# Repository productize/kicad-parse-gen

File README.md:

# kicad-parse-gen
rust kicad file code

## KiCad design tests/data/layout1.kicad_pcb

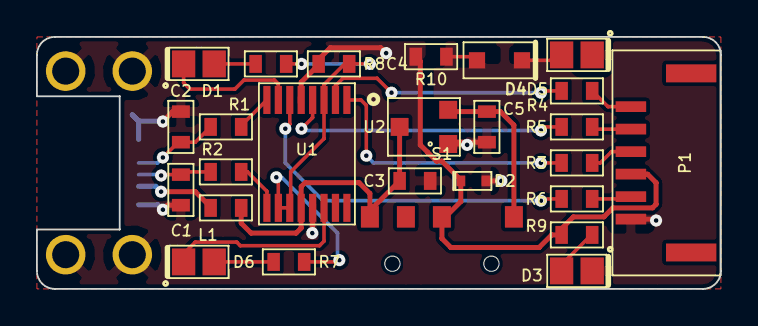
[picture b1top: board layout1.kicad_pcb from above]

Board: 2 copper layers, 38.0 x 14.0 mm, 27 parts (1 on the bottom side), 25 nets.

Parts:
C1, C2: 47pF; 0603_C
C3, C5: 4.7uF; 0603_C
C4: 100nF; 0603_C
D1, D3, D5, D6: LED; 0805_LED
D2: TVS; NXP-PESD-SOD523-SC-79
D4: 3V drop; NXP-SOD323-larger
J1: MICRO-USB-B-alt; USB-MICRO-B-FCI-10103593-0001LF
L1: FB; 0603_L
P1: CONN_01X06; JST-eGH-1.25mm-SMD-top-6
R1, R2, R3, R4, R5, R6: 27; 0603_R
R7, R8, R9, R10: 1k; 0603_R
S1: C_K_AYZ0103AGRLC_SP3T_Switch; C_K_AYZ0103AGRLC-ST3P-Switch
U1: FTDI-FT230X; FTDI-FT230X-SSOP16
U2: MCP1703-alt; SOT-23A_larger_pads

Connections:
+3.3VP: C4.1, R7.2, R8.2, U1.3, U1.10, U1.11
+3V3: C5.1, S1.4, U2.2
+5V: C3.1, L1.2, S1.1, U1.12, U2.3
/D+: C2.1, J1.3, R1.1
/D-: C1.1, J1.2, R2.1
/RXD: R5.1, U1.4
/RXD2: P1.5, R5.2
/TXD: R3.1, U1.1
/TXD2: P1.4, R3.2
/USB+: R1.2, U1.8
/USB-: R2.2, U1.9
/VBUS: J1.1, L1.1
/~CTS: R6.1, U1.6
/~CTS2: P1.2, R6.2
/~RTS: R4.1, U1.2
/~RTS2: P1.6, R4.2
/~RXLED: D6.2, U1.14
/~RXLED2: D6.1, R7.1
/~TXLED: D1.2, U1.7
/~TXLED2: D1.1, R8.1
GND: C1.2, C2.2, C3.2, C4.2, C5.2, D2.1, D3.2, D5.2, J1.5, J1.6, J1.7, J1.8, J1.9, J1.10, J1.11, P1.1, U1.5, U1.13, U2.1
unnamed: D3.1, R9.2
unnamed: D4.1, R10.2
unnamed: D4.2, D5.1
VCC: D2.2, P1.3, R9.1, R10.1, S1.3

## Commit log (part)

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2016-02-16 simplify Setup
2016-02-16 change Setup in HashMap
2016-02-16 bug fixes
2016-02-16 Setup::get
2016-02-16 update_element
2016-02-16 static
2016-02-17 more layer stuff
2016-02-18 0.3.0
2016-02-21 make clearly MIT licensed
2016-02-24 modify_components fun
2016-02-25 rework (WIP)
2016-02-26 cleanup
2016-03-02 introduce read_kicad_file
2016-03-03 add dummy project; expose parse methods
2016-03-03 capture more interesting data
2016-03-03 temp fix footprint parsing
2016-03-03 fix examples
2016-03-03 add identify
2016-03-03 pass in pathbuf towards schematic parser
2016-03-03 "fix"
2016-03-04 parse using trait (wip)
2016-03-04 sync
2016-03-07 parge page
2016-03-07 layers boilerplate
2016-03-07 use Layer from footprint
2016-03-07 parse Layers
2016-03-07 add Margin LayerType
2016-03-11 Setup parsing work
2016-03-11 implement gr_text and effects/justify
2016-03-11 add parsing of attr
2016-03-11 gr_line parsing
2016-03-11 implement Dimension
2016-03-14 more eleborate debugging, hide for layer
2016-03-14 support locked
2016-03-14 make angle optional in gr_line
2016-03-14 debugging
2016-03-14 mention that current parser breaks on tstamp on gr_line, gr_text, ...
2016-03-14 In1 In2
2016-03-14 fix pcbplotparams
2016-03-14 insert setup first
2016-03-14 more
2016-03-14 LAYERS
2016-03-14 fix setup elements
2016-03-14 get_module
2016-03-14 bounding box work
2016-03-15 bounding box and tstamp
2016-03-15 stamp pos in grtest
2016-03-15 iuse grelement for grtest
2016-03-15 fix typo
2016-05-18 update error handling
2016-05-26 add error.rs !
2016-05-26 fix error code
2016-05-26 make public
2016-05-27 clippy fixes (part 1)
2016-05-27 clippy fixes (part 3)
2016-05-27 needless borrow
2016-05-27 intosexp work
2016-05-27 intosexp (final) for footprint
2016-05-27 split up a bit
2016-05-27 split up further
2016-05-27 rework (busy)
2016-05-27 split up (WIP)
2016-05-31 step up to a custom kicad formatter
2016-05-31 use default
2016-05-31 kicadformatter (WIP)
2016-06-01 kicad formatter work
2016-06-01 cleanup/simplify
2016-06-01 kicad compatibility fixes
2016-06-02 kicad compat fixes
2016-06-02 into work
2016-06-02 cleanup, rework indent handling
2016-06-02 more output layout work
2016-06-06 rework indent
2016-06-07 readability improvements
2016-06-07 0.4.0
2016-06-07 layout formatting improvements; add no_connect
2016-06-07 make read_file public
2016-06-07 write file pub
2016-06-07 add write_layout
2016-06-15 support optional tstamp in dimension
2016-06-15 rudimetary (unparsed) support for AR Path entries in schematic
2016-06-16 add support for renaming net
2016-06-16 add test bins
2016-06-16 set_name String -> &str
2016-06-17 rename_net code
2016-06-17 formatting output fixes
2016-06-17 Bug #601
2016-08-01 fix italic/bold
2016-08-01 fix it
2016-08-05 remove explicit clippy stuff (cargo clippy works fine)
2016-08-05 some documentation and cleanup
2016-08-05 make read_file and write_file public again
2016-08-05 default() cleanup
2016-08-05 more default cleanup
2016-08-05 documentation and cleanups
2016-08-05 BoundingBox trait, move things around, documentation
2016-08-05 more documentation
2016-08-05 more docs
2016-08-05 documentation work; update .travis.yml
2016-08-05 small documentation fix
2016-08-05 fix travis authentication
2016-08-05 documentation
2016-08-05 more documentation; travis
2016-08-05 v0.6.0
2016-08-05 fix BoundingBox trait visibility
2016-08-05 cargo fmt fix
2016-08-05 use symbolic-expressions via crates
2016-08-05 cleanup repo
2016-08-17 0.7.1
2016-08-17 parse angles as floats
2016-08-17 0.7.2
2016-09-09 update License; remove unneeded dependency on rustc_serialize
2016-09-09 fix license
2016-09-09 update License; remove unneeded dependency on rustc_serialize
    fix license
2016-11-23 prepare for symbolic expressions v2
2016-11-23 build with serde
2016-11-23 fix compilation with stable
2016-11-23 fp_line
2016-11-24 fp_line & fp_poly
2016-12-02 fix build on stable compiler
2016-12-02 really fix compile
2016-12-02 oops
2016-12-06 add tracing support
2016-12-06 tracing support, more testing
2016-12-06 more testing
2016-12-06 ignore possible failure to initialize logging in testcases
2016-12-06 special handling of newtype within enum with same name
2016-12-13 make fields pub
2016-12-13 fix examples using CARGO_MANIFEST_DIR
2017-01-16 1.0.1: store and restore EELAYER In schematic
2017-01-17 fix spacing in output of schematic component (part2)
2017-01-17 update version
2017-01-17 optional diff_pair_gap and diff_pair_width in layout
2017-01-18 introduce Component::add_or_update_field; bump version
2017-01-18 more elaborate field update indication
2017-01-19 try! -> ?
2017-01-19 cargo fmt
2017-01-20 cleanup types for conversion methods
2017-01-20 Update documentation
2017-01-20 use docs.rs for docs
2017-01-20 use symbolic_expressions 4.0
2017-01-20 fix error handling for file reading
2017-01-23 use into in footprint
2017-01-23 rework layout with into()
2017-01-23 make examples work independant of directory
2017-01-23 use cleaner list gen api in footprint
2017-01-23 simplify Layer::from_string
2017-01-23 cargo clippy fixes
2017-01-24 move IterAtom stuff here from symbolic_expressions as it makes error handling much more elegant...
2017-01-24 release 3.0.2; use IterAtom wrapper for clean code
2017-01-24 4.0.7 or later patch level
2017-01-24 fix formatting of componentfield; add integration test for schematic
2017-01-24 fix gr_text ) on newline & newline after last module
2017-01-24 add newline at end of file
2017-01-24 write an extra newline before the first segment
2017-01-25 examples were actually tests; move files around to reflect that
2017-01-25 add symbol_lib parse_and_compare test
2017-01-25 actually set 3.0.4
2017-01-31 add support for parsing and generating aliases (#1059)
2017-01-31 bump version
2017-01-31 don't write temp file
2017-01-31 allow retrieval of list of modules from layout
2017-02-03 file handling with Path & PathBuf
2017-02-03 generalized util::write_file
2017-02-03 fix write_layout &Path
2017-02-03 all components func for schematic
2017-02-03 use Path isof PathBuf for schematic::parse_file
2017-02-07 bounding box for sheet
2017-02-07 make BoundingBox separate for schematic & layout
2017-02-07 4.1.5
2017-02-08 parse and save segment
2017-02-08 parse and gen via in layout
2017-02-08 support optional thermal_gap for pad in footprint
2017-02-08 add keepout area to test
2017-02-08 cleanup integration tests
2017-02-08 adjust trait implementation for #1076
2017-02-08 layer, tstamp, hatch for zone
2017-02-08 document parts of Zone that are still TODO
2017-02-08 min_thickness for zone
2017-02-08 cleaner zone parsing
2017-02-09 zone fill
2017-02-09 deal with kicad quoting in layout files
2017-02-09 polygon, filled_polygon and fill_segments for zone
2017-02-09 more IterAtom work
2017-02-10 use IterAtom as contained in symbolic_expressions
2017-02-10 IterAtom fixes
2017-02-10 more close and IterAtom
2017-02-10 4.1.8; IterAtom migration complete
2017-02-10 final part of implementation of Adjust for layout for #1076
2017-02-13 bounding box impromement for footprint Element
2017-02-13 coordinates in a Module are relative; fix bounding box code for it
2017-02-13 fix bounding block calculation
2017-02-14 bounding box code cleanup; 4.3.0
2017-02-28 3.3.1; update error-chain to 0.10; update env_logger to 0.4; update difference to 1.0
2017-03-07 improve bound handling
2017-03-23 Added support for Power, Mixed and Jumper layout layer types
    Fixes Redmine issue 1143
2017-03-23 Added support for pad clearance overrides
    Fixes Redmine issue 1144
2017-04-03 add wire and connection elements for schematic
2017-04-03 add some code to deal with unnamed nets
2017-04-03 oops; remove print!
2017-04-03 implement as_ref<str> for NetName
2017-04-03 introduce Draw type
2017-04-03 introduce Pin datastructure
2017-04-05 replace_block for NetName
2017-04-05 rework renaming of netnames utility methods
2017-04-06 bump version to 4.6.0
2017-04-06 add PartialEq for pure enum types
2017-04-06 support parsing no-connects
2017-04-10 add text examples
2017-04-10 text-type parsing and generation for schematic (unused yet)
2017-04-10 text parsing implementation
2017-05-31 add reference_ord
2017-05-31 4.7.3
2017-07-05 add fp-lib-table example
2017-07-05 fp-lib-table parsing (WIP)
2017-07-05 fp_lib_table parsing code
2017-07-06 fix public-ness of fp-lib-table datastructures
2017-07-06 ser/de timestamps as i64 isof string (API breaking change)
2017-07-07 derive PartialEq for part of the Module structs
2017-07-07 also derive PartialEq for Element
2017-07-07 custom implementation of PartialEq for FpText
2017-07-07 ignore At rotation for Pad in PartialEq
2017-07-07 don't consider Layer side for PartialEq
2017-07-07 fix inversion
2017-07-10 module flipping (WIP)
2017-07-10 make flip method public
2017-07-10 flip Xy's for Line
2017-07-10 expose get_rotation
2017-07-10 add rotation Trait
2017-07-10 5.0.9
2017-07-27 fix support for Wire types in schematic file format
2017-08-17 variable doesn't have to be mutable
2017-08-21 KLC work
2017-08-21 missing docs
2017-08-21 document, cleanup
2017-08-21 fix compilation
2017-08-21 only check pins for non-power non-graphics symbols
2017-08-22 start klc footprint subset
2017-08-22 basic checks for reference
2017-08-22 more reference and value tests
2017-08-22 check SMD placement
2017-08-22 document missing rest of KLC
2017-08-22 5.0.11
2017-08-22 have option to adjust some parts of the KLC checking to taste
2017-08-22 fix font_size handling
2017-08-22 make font thickness configurable also
2017-08-24 rework KLCConfig a bit
2017-08-24 rework Config naming
2017-08-24 rename (part 2)
2017-08-24 rename (part 3)
2017-08-24 fix reference2, insert when it doesn't exist
2017-08-24 fix attr smd
2017-08-24 introduce kicad::write_module
2017-08-30 CrtYd generation in fix
2017-08-30 fix y2
2017-08-30 only do bounding box for select things when calculating CrtYrd
2017-08-30 only use fab or pads for bounding box of compoment
2017-08-30 fix bound
2017-08-30 fix courtyard calculation
2017-08-30 add debug code
2017-08-30 fix pad bound for rot 180
2017-08-30 make rotation test a bit cleaner
2017-08-30 implement ofset like in KLC
2017-08-30 implement Element::Layer based on struct Layer
2017-08-31 fix bounding box for pad
2017-08-31 remove unused GetDrawingLayer trait
2017-09-04 cleanups
2017-09-25 use error-chain 0.11
2017-09-27 cleanup parse_split_quote_aware
2017-09-27 move Part and GrElement from lib to the related decoders
2017-09-27 parts cleanup
2017-09-27 reduce footprint::Part to what is left
2017-09-27 close iteratom's
2017-09-27 cleanup Via
2017-09-27 cleanup via code; add bind and micro via support
2017-09-27 improve parsing segment based on iteratom
2017-09-27 cleanup deserialization of Fill
2017-09-27 more de cleanup
2017-09-27 GrElement removal
2017-09-27 get rid of GrElement
2017-10-30 upgrade symbolic expressions to 5.0.2 simplifying error handling
2018-01-29 Fix interpretation of Rectangle background
2018-01-29 Implement Error and Display traits for KicadError
2018-09-18 allow ALIAS or $FPLIST to be in either order
    The Switch.lib shipping with current versions of kicad
    has some of these in a different order from the expectations
    of this crate, so add a simple loop that allows them to be
    in either order relative to each other.
2018-10-07 KiCad 5: Change expected file versions
2018-10-07 KiCad 5: No links, no_connects and area in layout info anymore
2018-10-07 KiCad 5: via now has tstamp
2018-10-07 KiCad 5: module now has solder_paste_margin
2018-10-07 KiCad 5: pad now has thermal_width
2018-10-07 KiCad 5: model now has offset iof at (but both can be used)
2018-10-09 KiCad 5: Add support for sym-lib-table
2018-12-11 add connect pad type
2019-05-21 symbol_lib: Do not assume $FPLIST comes before ALIAS
2019-05-29 Add optional field status to via
    Apparently some layout files contain (via (status <n>)).
2019-08-22 schematic: Allow for -1 in component rotation field
2019-08-22 schematic: Do not skip alleged position line if it has 4 elements
    The "position" line can apparently begin with other number than
    1 making the original code confuse a "position" line with a
    genuine "rotation" line.
2019-08-22 schematic: Skip component lines starting with 2-9
    Apparently these lines are quite common now :-)

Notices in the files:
tests/data/layout1.kicad_pcb:
(c) 2015 productize
